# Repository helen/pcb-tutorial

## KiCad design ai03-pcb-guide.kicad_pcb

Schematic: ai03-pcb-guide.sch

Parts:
C1, C2, C3: 0.1uF; C_0805_2012Metric
C4, C5: 22pF; C_0805_2012Metric
C6: 10uF; C_0805_2012Metric
C7: 1uF; C_0805_2012Metric
D1, D2, D3, D4: SOD-123; D_SOD-123
F1: 500mA; Fuse_1206_3216Metric
MX1, MX2, MX3, MX4: MX-NoLED; MX-1U-NoLED
R1, R2: 22; R_0805_2012Metric
R3, R4: 10k; R_0805_2012Metric
SW1: SW_Push; SKQG-1155865
U1: ATmega32U4-AU; TQFP-44_10x10mm_P0.8mm
USB1: Molex-0548190589
Y1: 16MHz; Crystal_SMD_3225-4Pin_3.2x2.5mm

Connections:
+5V: C1.1, C2.1, C3.1, C6.1, F1.1, R3.1, U1.2 (UVCC), U1.7 (VBUS), U1.14 (VCC), U1.24 (AVCC), U1.34 (VCC), U1.44 (AVCC)
COL0: MX1.1, MX2.1, U1.27 (PD7)
COL1: MX3.1, MX4.1, U1.28 (PB4)
D+: R2.2, USB1.3
D-: R1.2, USB1.4
GND: C1.2, C2.2, C3.2, C4.2, C5.2, C6.2, C7.2, R4.1, SW1.1, U1.5 (UGND), U1.15 (GND), U1.23 (GND), U1.35 (GND), U1.43 (GND), USB1.1
unnamed: C4.1, U1.17 (XTAL1), Y1.1
unnamed: C5.1, U1.16 (XTAL2), Y1.3
unnamed: C7.1, U1.6 (UCAP)
unnamed: D1.2, MX1.2
unnamed: D2.2, MX2.2
unnamed: D3.2, MX3.2
unnamed: D4.2, MX4.2
unnamed: R1.1, U1.3 (D-)
unnamed: R2.1, U1.4 (D+)
unnamed: R3.2, SW1.2, U1.13 (~RESET)
unnamed: R4.2, U1.33 (~HWB~/PE2)
unnamed: Y1.2, Y1.4
ROW0: D1.1, D3.1, U1.29 (PB5)
ROW1: D2.1, D4.1, U1.30 (PB6)
VCC: F1.2, USB1.5

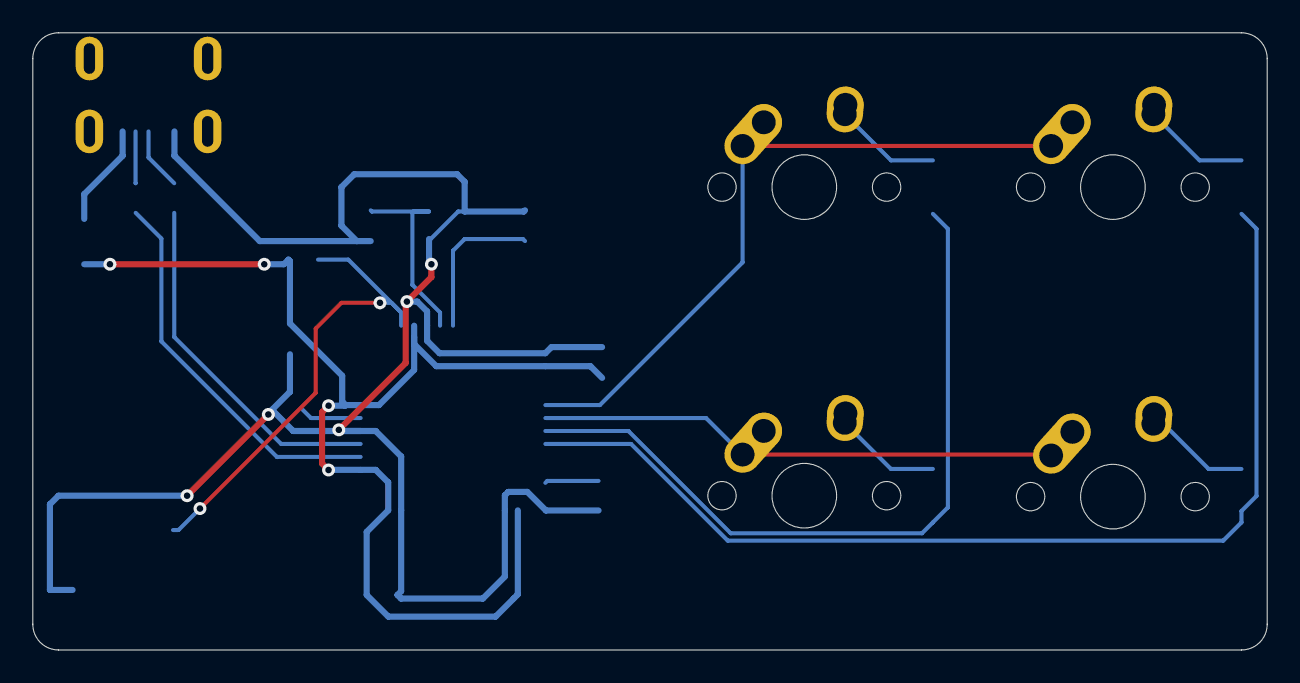
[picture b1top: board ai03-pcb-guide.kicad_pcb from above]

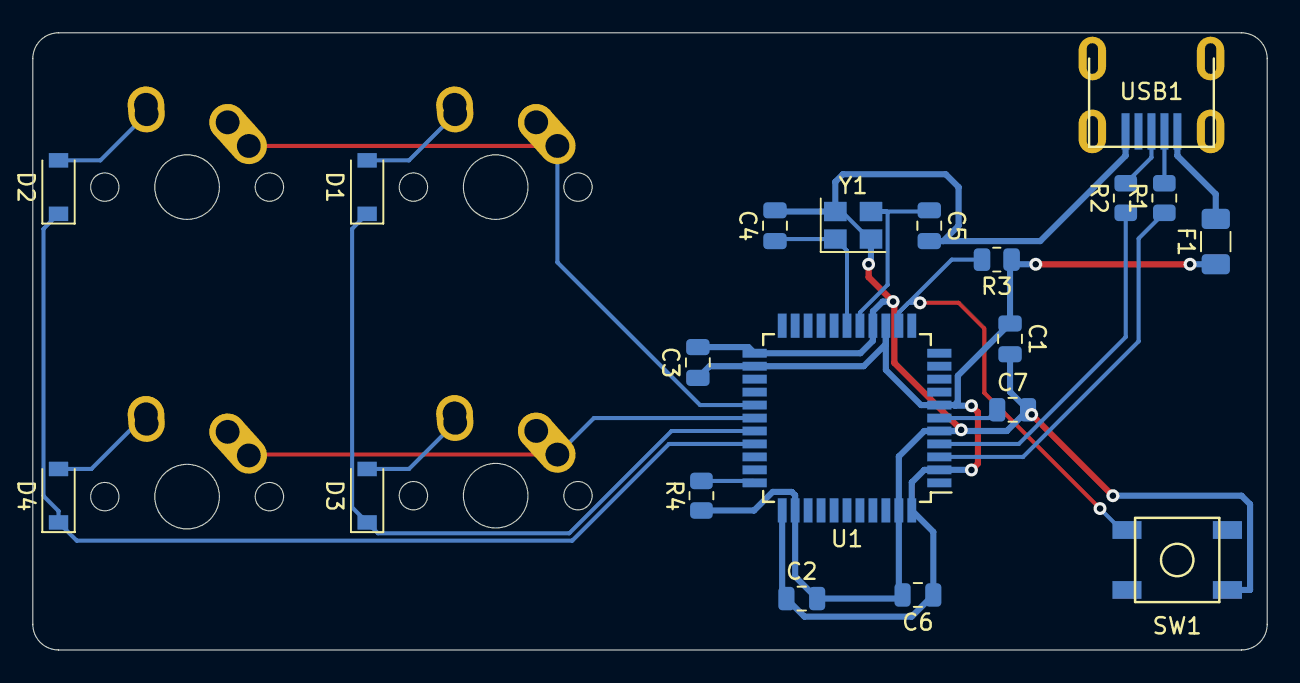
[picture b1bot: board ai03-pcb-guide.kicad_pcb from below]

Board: 2 copper layers, 76.2 x 38.1 mm, 24 parts (20 on the bottom side), 21 nets.

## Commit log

2021-02-22 Initial project setup
2021-02-22 Add submodules
2021-02-22 Import symbol libraries
2021-02-22 5V and GND
2021-02-22 First components
2021-02-22 Complete MCU
2021-02-22 USB Mini-B connector
2021-02-22 Switch schematic
2021-02-22 Assigning footprints
2021-02-23 Prep PCB layout
2021-02-23 Route components
2021-02-23 Route to switches
